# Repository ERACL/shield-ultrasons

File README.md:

Shield-ultrasons
================

Shield ultrasons - Shield pour connecter les capteurs ultrasons

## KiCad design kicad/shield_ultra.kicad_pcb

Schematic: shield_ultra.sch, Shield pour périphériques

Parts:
D1, D2, D3: 3.3V; D_A-405_P10.16mm_Horizontal
J1, J5, J7: Ultrason; Molex_KK-6410-04_04x2.54mm_Straight
J2, J4, J6: IR; Molex_KK-6410-03_03x2.54mm_Straight
J3: Accel; Molex_KK-6410-04_04x2.54mm_Straight
J8, J9: Ultrason; Molex_KK-6410-03_03x2.54mm_Straight
R1, R2: 10K; R_Axial_DIN0204_L3.6mm_D1.6mm_P7.62mm_Horizontal
U1: Conn_shield; conn_shield

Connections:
+3V3: J3.1, R1.1, R2.1, U1.V31 (3.3V), U1.V32 (3.3V), U1.V33 (3.3V)
+5V: J1.4, J2.1, J4.1, J5.4, J6.1, J7.4, J8.2, J9.2, U1.V51 (5V), U1.V52 (5V), U1.V53 (5V)
/A0: D1.1, J2.3, U1.A0 (RA0)
/A1: D2.1, J4.3, U1.A1 (RA1)
/B0: J8.3, U1.B0 (RB0)
/B1: J9.3, U1.B1 (RB1)
/B2: J1.3, J3.3, J5.3, J7.3, R2.2, U1.B2 (RB2)
/B3: J1.2, J3.4, J5.2, J7.2, R1.2, U1.B3 (RB3)
/B4: D3.1, J6.3, U1.B4
GND: D1.2, D2.2, D3.2, J1.1, J2.2, J3.2, J4.2, J5.1, J6.2, J7.1, J8.1, J9.1, U1.G1 (GND), U1.G2 (GND), U1.G3 (GND), U1.G4 (GND), U1.G5 (GND), U1.G6 (GND)

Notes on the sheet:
Connecteurs du shield
RB3 = I2C CLK RB2 = I2C DATA
Relier L1 et V34 si besoin d'un PIC 44 pattes
Pull up I2C
Connexion des capteurs

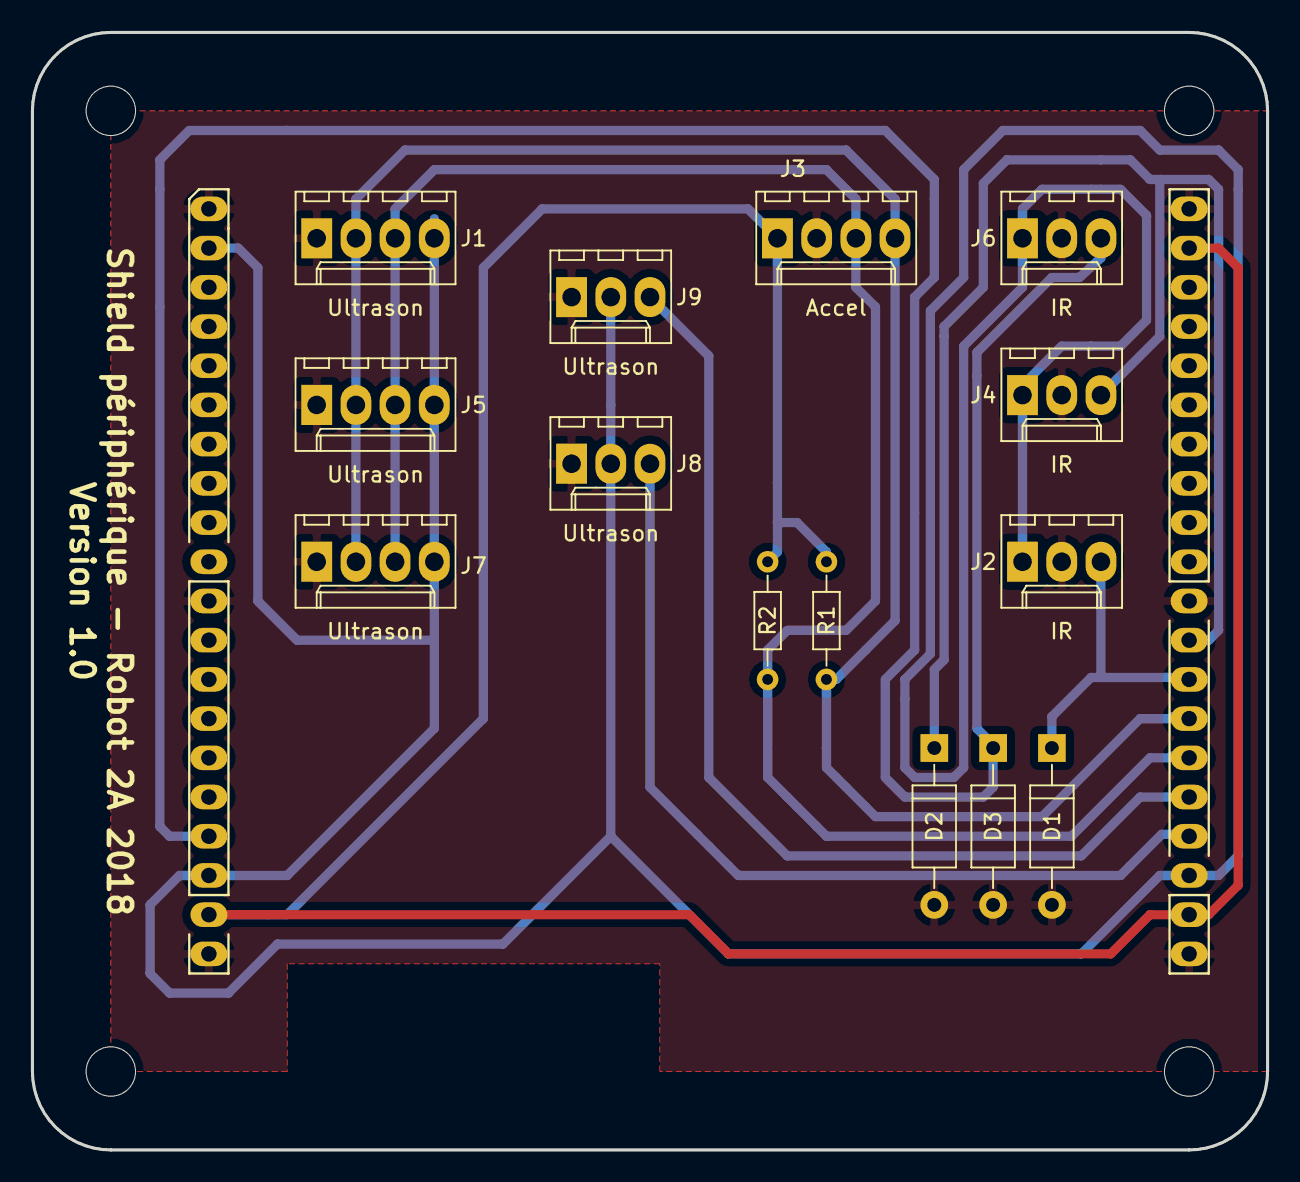
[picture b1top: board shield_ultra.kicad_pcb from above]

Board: 2 copper layers, 80.0 x 72.4 mm, 15 parts (0 on the bottom side), 10 nets.

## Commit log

2018-04-10 Mise en forme du fichier README.md
2018-04-10 Ignorer dossier export
2018-04-10 Premier jet
2018-04-20 Modification connexions capteurs
2018-04-22 Ignorer fichiers Gerber
2018-04-22 Finitions avant release
2018-04-22 Mise à jour des cartouches en vue de la release
